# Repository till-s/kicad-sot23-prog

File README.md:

# kicad-sot23-prog

Programming Socket for Use with Azoteq CT210.

Uses a wells-499-p44-20 or similar socket.

LICENSE: public domain

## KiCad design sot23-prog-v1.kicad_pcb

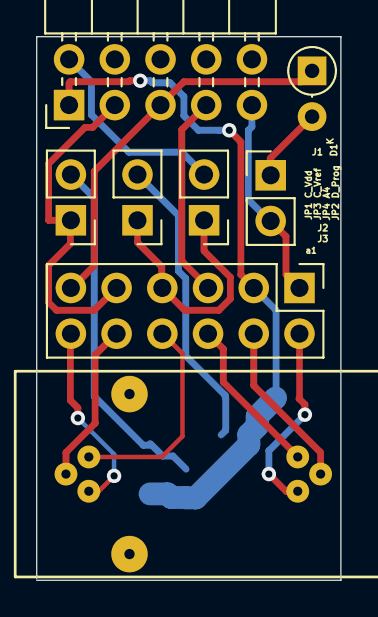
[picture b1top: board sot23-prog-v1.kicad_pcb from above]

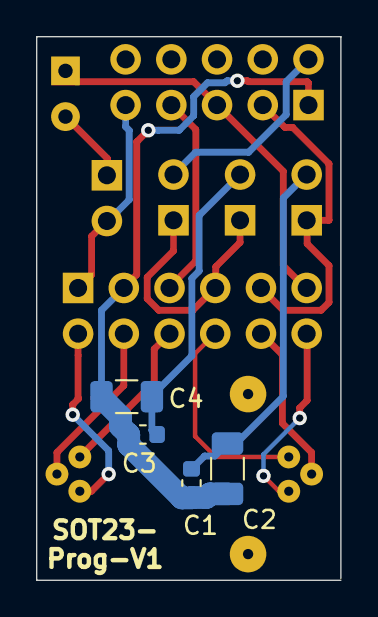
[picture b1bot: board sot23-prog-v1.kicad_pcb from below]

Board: 2 copper layers, 16.9 x 30.2 mm, 12 parts (4 on the bottom side), 16 nets.

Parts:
C1, C3: 100pF; C_0603_1608Metric
C2, C4: 1uF; C_1206_3216Metric
D1: DIODE; D_DO-35_SOD27_P2.54mm_Vertical_AnodeUp
J1: Conn_02x05_Odd_Even; PinHeader_2x05_P2.54mm_Horizontal
J2: Conn_02x06_Row_Letter_First; PinHeader_2x06_P2.54mm_Vertical_parallel_rows
J3: Conn_02x03_Counter_Clockwise; wells-499-p44-20
JP1 C_Vdd: VDD_Cap; PinHeader_1x02_P2.54mm_Vertical
JP2 D_Prog: D_Prog; PinHeader_1x02_P2.54mm_Vertical
JP3 C_Vref: Vref_Cap; PinHeader_1x02_P2.54mm_Vertical
JP4 A4: Conn_a4; PinHeader_1x02_P2.54mm_Vertical

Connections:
unnamed: C1.1, C2.1, JP1 C_Vdd.2
unnamed: C1.2, C2.2, C3.2, C4.2, J1.1, J2.a2
unnamed: C3.1, C4.1, JP3 C_Vref.2
unnamed: D1.1, J1.5, J2.a6
unnamed: D1.2, JP2 D_Prog.1
unnamed: J1.2, JP4 A4.2
unnamed: J1.3, J2.a5, JP1 C_Vdd.1
unnamed: J1.7, J2.a3
unnamed: J1.9, J2.a1, JP2 D_Prog.2
unnamed: J2.a4, JP3 C_Vref.1, JP4 A4.1
unnamed: J2.b1, J3.1
unnamed: J2.b2, J3.2
unnamed: J2.b3, J3.3
unnamed: J2.b4, J3.4
unnamed: J2.b5, J3.5
unnamed: J2.b6, J3.6

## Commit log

2023-07-03 added files to git
2023-07-03 schematic: added comment
